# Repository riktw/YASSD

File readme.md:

The files for the YASSD, Yet Another Seven Segment Display.
Everything is open source licensed, GPLv3 for software and CC BY-SA 4.0 for hardware unless otherwise stated.
The hardware is designed in KiCad and the software in the AC6 System Workbench. Schematic in PDF and compiled binaries can be found in the HW and SW folder as well.

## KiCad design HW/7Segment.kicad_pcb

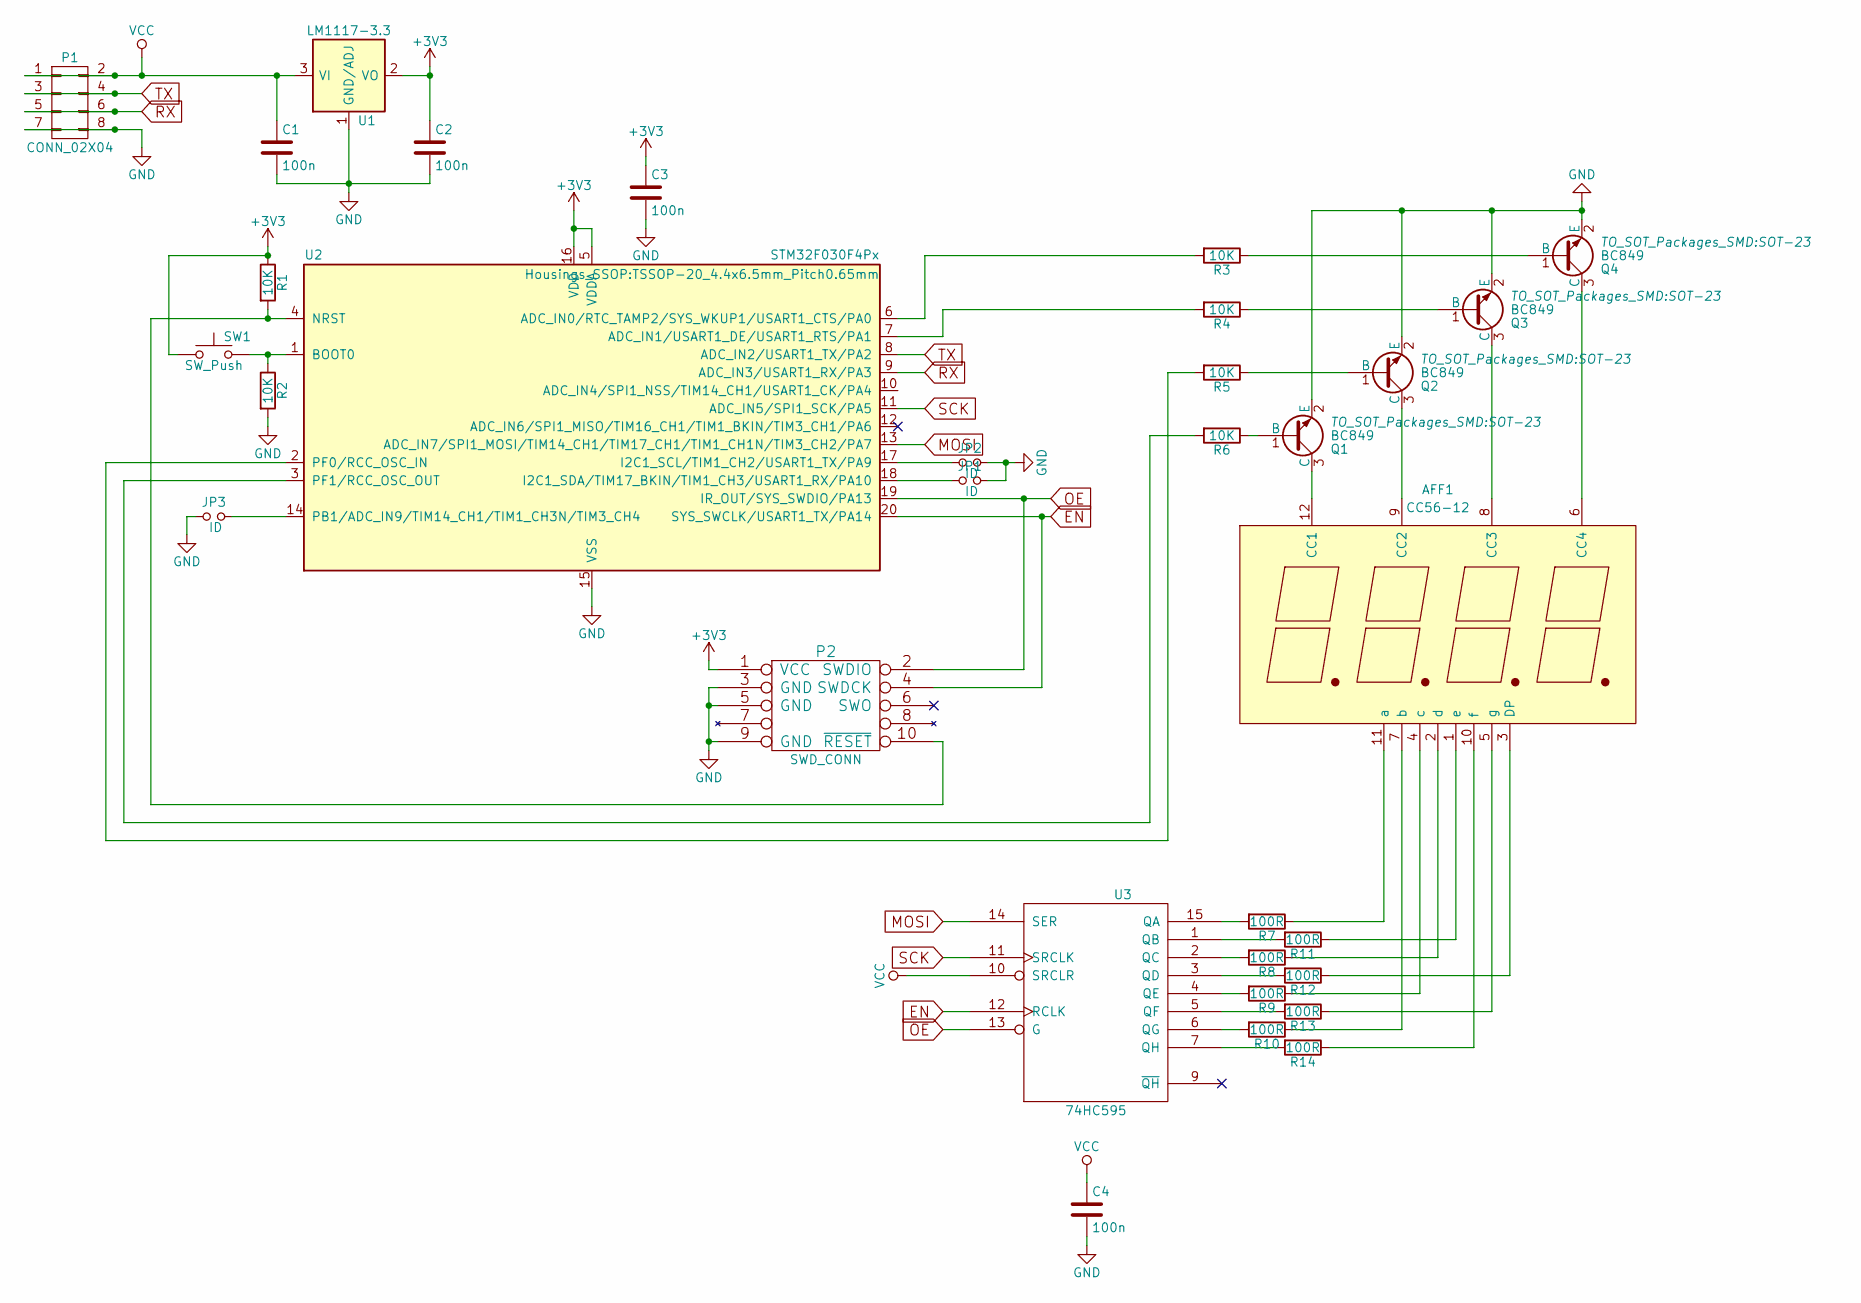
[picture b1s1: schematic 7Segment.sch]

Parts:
AFF1: CC56-12; Cx56-12
C1, C2, C3, C4: 100n; C_0603_HandSoldering
JP1, JP2, JP3: ID; R_0402
P1: CONN_02X04; Pin_Header_Straight_2x04
P2: SWD_CONN
Q1, Q2, Q3, Q4: BC849; SOT-23
R1, R2, R3, R4, R5, R6: 10K; R_0603_HandSoldering
R7, R8, R9, R10, R11, R12, R13, R14: 100R; R_0603_HandSoldering
SW1: SW_Push; SW_SPST_FSMSM
U1: LM1117-3.3; SOT-223
U2: STM32F030F4Px; TSSOP-20_4.4x6.5mm_Pitch0.65mm
U3: 74HC595; SOIC-16_3.9x9.9mm_Pitch1.27mm

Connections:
+3V3: C2.1, C3.1, P2.1 (VCC), R1.1, SW1.1, U1.2 (VO), U1.4 (VO), U2.5 (VDDA), U2.16 (VDD)
EN: P2.4 (SWDCK), U2.20 (SYS_SWCLK/USART1_TX/PA14), U3.12 (RCLK)
GND: C1.2, C2.2, C3.2, C4.2, JP1.2, JP2.2, JP3.1, P1.7, P1.8, P2.3 (GND), P2.5 (GND), P2.9 (GND), Q1.2 (E), Q2.2 (E), Q3.2 (E), Q4.2 (E), R2.2, U1.1 (GND/ADJ), U2.15 (VSS), U3.8 (GND)
MOSI: U2.13 (ADC_IN7/SPI1_MOSI/TIM14_CH1/TIM17_CH1/T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), U3.14 (SER)
unnamed: AFF1.1 (e), R11.1
unnamed: AFF1.2 (d), R8.1
unnamed: AFF1.3 (DP), R12.1
unnamed: AFF1.4 (c), R9.1
unnamed: AFF1.5 (g), R13.1
unnamed: AFF1.6 (CC4), Q4.3 (C)
unnamed: AFF1.7 (b), R10.1
unnamed: AFF1.8 (CC3), Q3.3 (C)
unnamed: AFF1.9 (CC2), Q2.3 (C)
unnamed: AFF1.10 (f), R14.1
unnamed: AFF1.11 (a), R7.1
unnamed: AFF1.12 (CC1), Q1.3 (C)
unnamed: JP1.1, U2.18 (I2C1_SDA/TIM17_BKIN/TIM1_CH3/USART1_RX/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)
unnamed: JP2.1, U2.17 (I2C1_SCL/TIM1_CH2/USART1_TX/PA9)
unnamed: JP3.2, U2.14 (PB1/ADC_IN9/TIM14_CH1/TIM1_CH3N/TIM3_CH4)
unnamed: P2.10 (~RESET), R1.2, U2.4 (NRST)
unnamed: Q1.1 (B), R6.1
unnamed: Q2.1 (B), R5.1
unnamed: Q3.1 (B), R4.1
unnamed: Q4.1 (B), R3.1
unnamed: R2.1, SW1.2, U2.1 (BOOT0)
unnamed: R3.2, U2.6 (ADC_IN0/RTC_TAMP2/SYS_WKUP1/USART1_CTS/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)
unnamed: R4.2, U2.7 (ADC_IN1/USART1_DE/USART1_RTS/PA1)
unnamed: R5.2, U2.2 (PF0/RCC_OSC_IN)
unnamed: R6.2, U2.3 (PF1/RCC_OSC_OUT)
unnamed: R7.2, U3.15 (QA)
unnamed: R8.2, U3.2 (QC)
unnamed: R9.2, U3.4 (QE)
unnamed: R10.2, U3.6 (QG)
unnamed: R11.2, U3.1 (QB)
unnamed: R12.2, U3.3 (QD)
unnamed: R13.2, U3.5 (QF)
unnamed: R14.2, U3.7 (QH)
OE: P2.2 (SWDIO), U2.19 (IR_OUT/SYS_SWDIO/PA13), U3.13 (G)
RX: P1.5, P1.6, U2.9 (ADC_IN3/USART1_RX/PA3)
SCK: U2.11 (ADC_IN5/SPI1_SCK/PA5), U3.11 (SRCLK)
TX: P1.3, P1.4, U2.8 (ADC_IN2/USART1_TX/PA2)
VCC: C1.1, C4.1, P1.1, P1.2, U1.3 (VI), U3.10 (SRCLR), U3.16 (VCC)

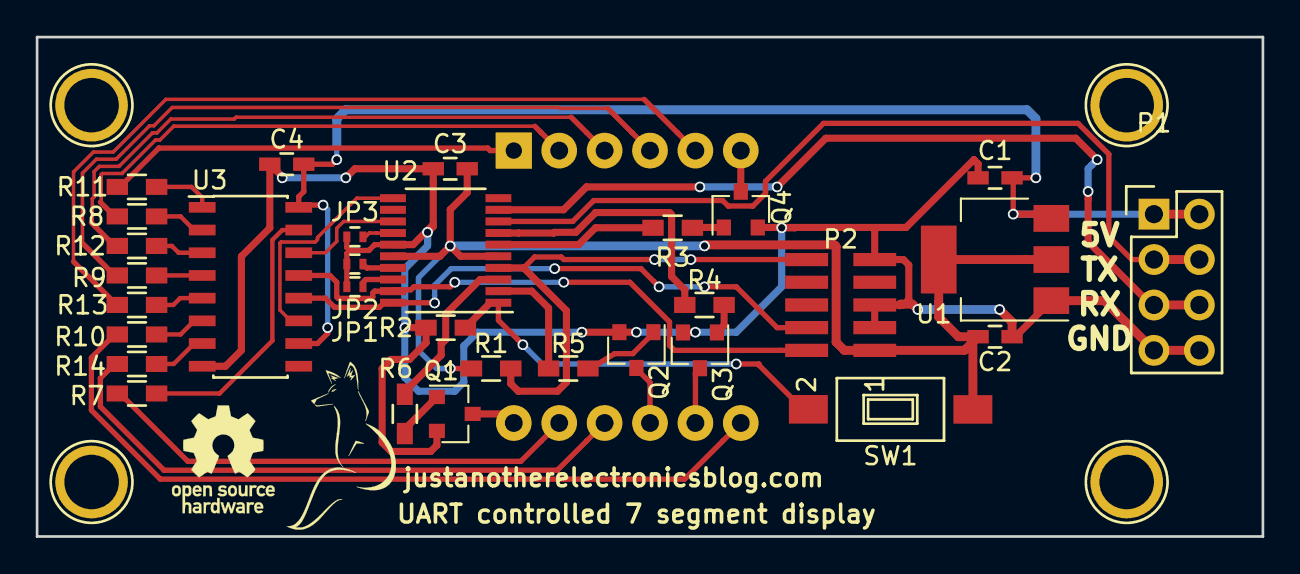
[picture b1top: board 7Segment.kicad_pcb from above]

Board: 2 copper layers, 68.6 x 27.9 mm, 32 parts (1 on the bottom side), 42 nets.

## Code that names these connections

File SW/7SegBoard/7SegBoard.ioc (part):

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Mcu.Name=STM32F031F(4-6)Px
Mcu.Package=TSSOP20
Mcu.UserName=STM32F031F6Px
PA0.GPIOParameters=GPIO_Label
PA0.GPIO_Label=Segment1
PA0.Signal=GPIO_Output
PA1.GPIOParameters=GPIO_Label
PA1.GPIO_Label=Segment2
PA1.Signal=GPIO_Output
PA10.GPIOParameters=GPIO_PuPd,GPIO_Label
PA10.GPIO_Label=ID2
PA10.GPIO_PuPd=GPIO_PULLUP
PA10.Signal=GPIO_Input
PA13.GPIOParameters=GPIO_Label
PA13.GPIO_Label=OutputEnable
PA13.Signal=GPIO_Output
PA14.GPIOParameters=GPIO_Label
PA14.GPIO_Label=STREG
PA14.Signal=GPIO_Output
PA2.Mode=Asynchronous
PA2.Signal=USART1_TX
PA3.Mode=Asynchronous
PA3.Signal=USART1_RX
PA5.Mode=Full_Duplex_Master
PA5.Signal=SPI1_SCK
PA6.Mode=Full_Duplex_Master
PA6.Signal=SPI1_MISO
PA7.Mode=Full_Duplex_Master
PA7.Signal=SPI1_MOSI
PA9.GPIOParameters=GPIO_PuPd,GPIO_Label
PA9.GPIO_Label=ID1
PA9.GPIO_PuPd=GPIO_PULLUP
PA9.Signal=GPIO_Input
PB1.GPIOParameters=GPIO_PuPd,GPIO_Label
PB1.GPIO_Label=ID0
PB1.GPIO_PuPd=GPIO_PULLUP
PB1.Signal=GPIO_Input
PF0-OSC_IN.GPIOParameters=GPIO_Label
PF0-OSC_IN.GPIO_Label=Segment3
PF0-OSC_IN.Signal=GPIO_Output
PF1-OSC_OUT.GPIOParameters=GPIO_Label
PF1-OSC_OUT.GPIO_Label=Segment4
PF1-OSC_OUT.Signal=GPIO_Output
board=7SegBoard
